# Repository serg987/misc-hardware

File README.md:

# misc-hardware

Collection of small hardware projects and KiCad designs developed as experimental ones

## Projects

- [mllse-m2-air-breakout-board](./mllse-m2-air-breakout-board/)
  - Breakout board and modification guide for the MLLSE M2 Air mini PC. Provides two full-size M.2 Key-B SATA slots and 
one M.2 Key-M PCIe x1 slot, includes KiCad project, BOM, gerbers, and step-by-step modification instructions.

- [radxa_a5e_m2_to_rasp_pcie](./radxa_a5e_m2_to_rasp_pcie/)
  - M.2 Key-M to Raspberry Pi PCIe adapter for the Radxa A5E SBC. Allows using Raspberry Pi PCIe HATs via a 
Raspberry Pi PCIe FPC cable.

## How to use

Each project contains its own `readme.md` with detailed information, KiCad project files, and media. 
Open the subproject folder and read its `readme.md` for design details, BOM, and assembly or modification instructions.

## License

This repository is covered by the project LICENSE. See `LICENSE` in the repository root for details.

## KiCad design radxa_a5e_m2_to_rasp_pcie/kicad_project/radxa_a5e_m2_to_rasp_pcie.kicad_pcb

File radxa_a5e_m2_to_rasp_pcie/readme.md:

# M.2 Key M to Raspberry Pi PCIe adapter

Allows use of Raspberry Pi HATs with the Radxa A5E SBC. Requires a Raspberry Pi PCIe FPC cable at least 40 mm long.

The board was manufactured and electrically tested — it is recognized by the Radxa A5E. Due to Radxa's limited 
third‑party support, development will not continue. The design can still serve as a baseline for other projects.

## BOM

- 16‑pin 0.5 mm 'bottom' FPC connector  
- Optional 5 V power-supply connector — any 2‑pin 1.0 mm pitch SMD connector

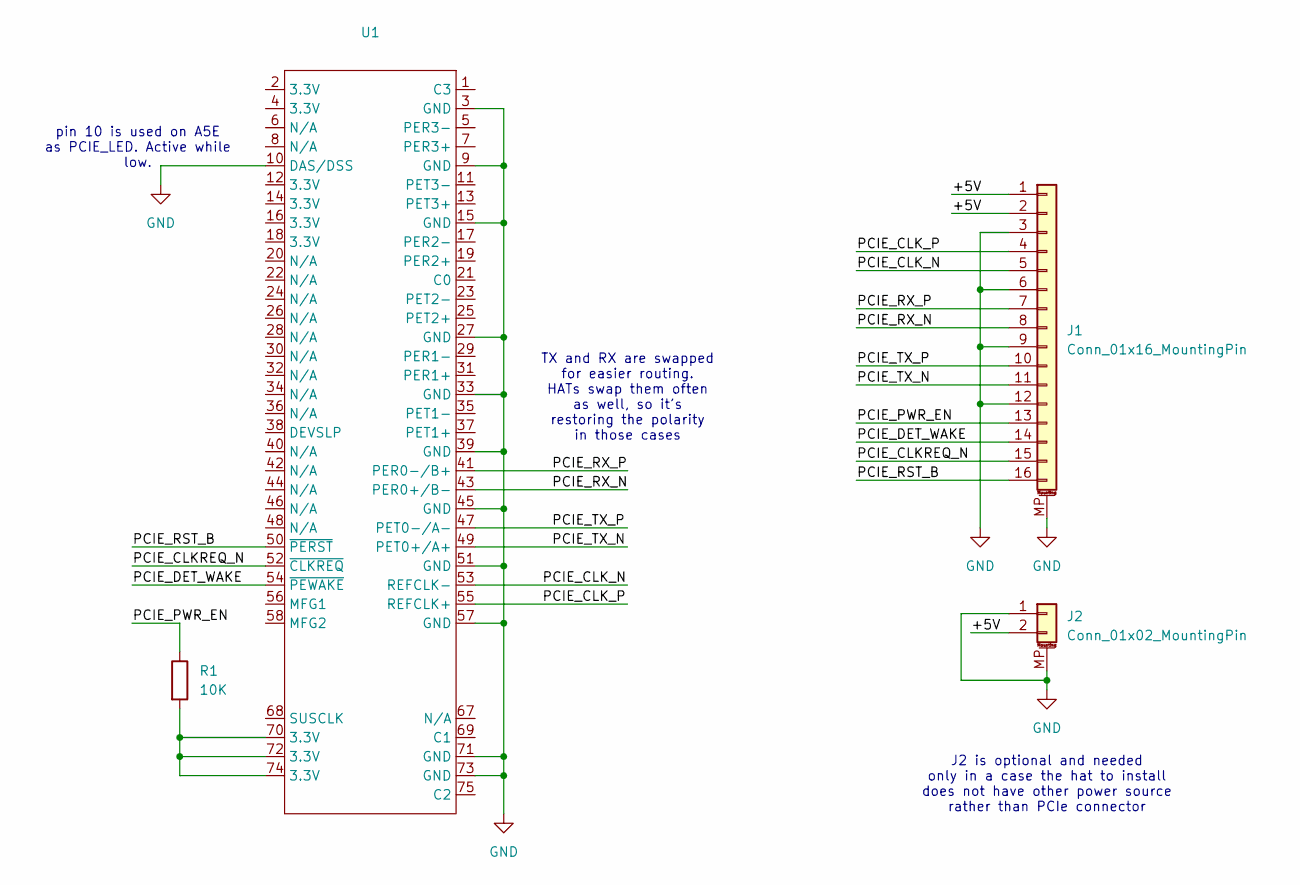
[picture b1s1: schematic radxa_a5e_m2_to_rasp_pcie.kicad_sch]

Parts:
J1: Conn_01x16_MountingPin; Amphenol_F32Q-1A7x1-11016_1x16-1MP_P0.5mm_Horizontal-revers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
J2: Conn_01x02_MountingPin; JST_SH_SM02B-SRSS-TB_1x02-1MP_P1.00mm_Horizontal
R1: 10K; R_1206_3216Metric_Pad1.30x1.75mm_HandSolder
U1: NGFF_M_LONG_NO_MASK

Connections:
/+5V: J1.1, J1.2, J2.2
/PCIE_CLKREQ_N: J1.15, U1.52 (~CLKREQ)
/PCIE_CLK_N: J1.5, U1.53 (REFCLK-)
/PCIE_CLK_P: J1.4, U1.55 (REFCLK+)
/PCIE_DET_WAKE: J1.14, U1.54 (~PEWAKE)
/PCIE_PWR_EN: J1.13, R1.1
/PCIE_RST_B: J1.16, U1.50 (~PERST)
/PCIE_RX_N: J1.8, U1.43 (PER0+/B-)
/PCIE_RX_P: J1.7, U1.41 (PER0-/B+)
/PCIE_TX_N: J1.11, U1.49 (PET0+/A+)
/PCIE_TX_P: J1.10, U1.47 (PET0-/A-)
GND: J1.3, J1.6, J1.9, J1.12, J1.MP (MountPin), J2.1, J2.MP (MountPin), U1.3 (GND), U1.9 (GND), U1.10 (DAS/DSS), U1.15 (GND), U1.27 (GND), U1.33 (GND), U1.39 (GND), U1.45 (GND), U1.51 (GND), U1.57 (GND), U1.71 (GND), U1.73 (GND)
unnamed: R1.2, U1.70 (3.3V), U1.72 (3.3V), U1.74 (3.3V)

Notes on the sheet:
TX and RX are swapped for easier routing. HATs swap them often as well, so it's restoring the polarity in those cases
pin 10 is used on A5E as PCIE_LED. Active while low.
J2 is optional and needed only in a case the hat to install does not have other power source rather than PCIe connector

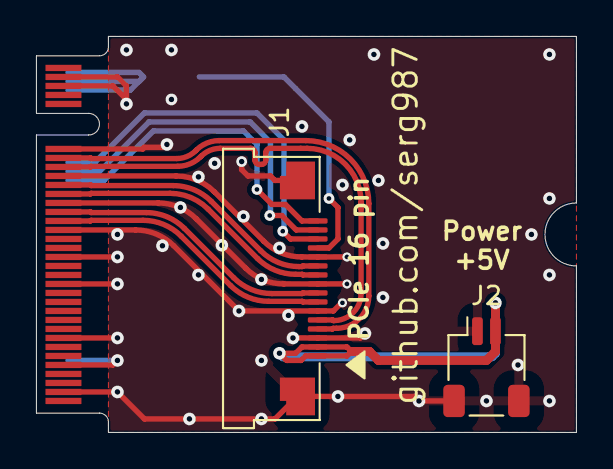
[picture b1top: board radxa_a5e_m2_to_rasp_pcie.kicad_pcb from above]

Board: 2 copper layers, 30.0 x 22.0 mm, 4 parts (1 on the bottom side), 13 nets.

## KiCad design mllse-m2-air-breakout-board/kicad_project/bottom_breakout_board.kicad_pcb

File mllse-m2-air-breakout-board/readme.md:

# M.2 Breakout Board for MLLSE M2 Air Mini PC

This project contains the design files and instructions for a breakout board that significantly expands the I/O 
capabilities of the MLLSE M2 Air Mini PC, a compact and affordable x86 machine ideal for homelab projects.

## Table of Contents

- [Motivation](#motivation)
- [Project Overview](#project-overview)
- [Disclaimer](#-disclaimer)
- [Compatibility](#compatibility)
- [The Breakout Board](#the-breakout-board)
  - [Features](#features)
  - [Onboard Power Supply](#onboard-power-supply)
  - [PCB Manufacturing](#pcb-manufacturing)
- [Mainboard Modification Guide](#mainboard-modification-guide)
  - [Step 1: Sourcing 12V Power](#step-1-sourcing-12v-power)
  - [Step 2: Preparing the PCIe Interface](#step-2-preparing-the-pcie-interface)
  - [Step 3: Preparing the Secondary SATA Interface](#step-3-preparing-the-secondary-sata-interface)
- [Bill of Materials (BOM)](#bill-of-materials-bom)
- [Known Issues](#known-issues)

## Motivation

Low-power, small-form-factor computers like mini PCs and Single-Board Computers (SBCs) are excellent choices for 
homelab setups. However, the market can be challenging to navigate. Powerful x86-based options with standard interfaces 
like PCIe and SATA are often expensive, while many non-x86 alternatives lack robust software support and documentation 
(with the notable exception of the Raspberry Pi).

A series of inexpensive Chinese mini PCs, such as the MLLSE M2 Air (based on Intel N4000/N3350 CPUs), offer a 
compelling alternative. They are passively cooled, affordable, and being native x86, they run most software without 
compatibility concerns. For a price comparable to a Raspberry Pi 5 kit, you get a complete system with an enclosure, 
heatsink, and power supply.

However, their primary limitation is a restrictive set of internal interfaces:
- A single M.2 Key-B slot (SATA only) that physically fits only small `<2242` modules.
- A proprietary, unpopulated SATA connector.
- No accessible PCIe lanes for expansion.

This project was born out of a desire to unlock the true potential of this hardware, transforming it from a limited 
device into a versatile server platform.

## Project Overview

This breakout board is designed to overcome the MLLSE M2 Air's I/O limitations. By interfacing with the existing M.2 
slot and repurposing connectors on the mainboard, it provides:

- **Two (2) full-size 2280 M.2 Key-B SATA slots.**
- **One (1) full-size 2280 M.2 Key-M PCIe x1 slot.**

With this board, the mini PC becomes a powerful and flexible platform. It can be used as a Network Video Recorder 
(NVR) with a Google Coral TPU in the PCIe slot and two SATA drives for storage, or as a mini NAS with up to three 
storage devices.

---

## ⚠️ Disclaimer

**This is an advanced hardware modification project that requires significant technical skill, including fine-pitch 
soldering with a hot air station. There is a high risk of permanently damaging your mini PC.**

**Proceed at your own risk. The author of this project assumes no liability for any damage to your equipment, lost time, 
or any other losses incurred while attempting this modification. Please evaluate your skills and equipment before 
starting.**

---

## Compatibility

This breakout board was designed specifically for the **MLLSE M2 Air, PCB version `MX-GB07 V100 20191009`**.

It is highly likely that other PCB versions or models based on different CPUs (e.g., N3350) have different layouts, 
and this board will **not** be compatible with them. While those boards may offer similar modification opportunities, 
they would require a new PCB to be designed from scratch.

## The Breakout Board

The breakout board neatly integrates into the system by plugging into the mainboard's original M.2 slot and is secured 
with M2 standoffs.

### Features

- **PCIe M.2 Key-M Slot:** Taps into the PCIe lanes originally used by the onboard Wi-Fi/Bluetooth module.
- **Two SATA M.2 Key-B Slots:** One slot uses the mainboard's original M.2 connection, and the second uses the 
unpopulated SATA header.
- **Onboard Power Supply:** A DC-DC buck converter provides the stable 3.3V power required for all three M.2 devices.

### Onboard Power Supply

The board includes a DC-DC buck converter based on the FR9889 IC to step down the mainboard's 12V input to the 3.3V 
needed by the M.2 devices. The converter's enable pin is connected to the 3.3V line of the mainboard's M.2 slot, 
ensuring the breakout board powers on and off with the host system.

**🚨 CRITICAL PRECAUTION: After assembling the breakout board, always test the output voltage of the DC-DC converter 
*before* installing any M.2 devices. Ensure it provides a stable 3.3V.**

### PCB Manufacturing

The PCB is designed to be 100x100mm to take advantage of promotional pricing from many manufacturers. It is essential 
that the board is manufactured with a **thickness of 0.8mm**.

The Gerbers can be found in the `/gerbers` directory. You can order the board from PCBWAY with this 
[link](https://www.pcbway.com/project/shareproject/MLLSE_M2_Air_Triple_M_2_Expansion_Breakout_Board_1323e575.html).

## Mainboard Modification Guide

### Step 1: Sourcing 12V Power

The easiest place to get a 12V supply for the breakout board is directly from the main DC input jack.

### Step 2: Preparing the PCIe Interface

This is the most challenging part of the modification. It requires desoldering the onboard Wi-Fi/Bluetooth module to 
access the PCIe lanes.

1.  **Remove the Wi-Fi Module:** Use a hot air station to carefully desolder the Wi-Fi module. Be aware of the multiple 
ground pads underneath the module and the many small passive components surrounding it. Avoid damaging the 
signal pads.
2.  **Solder the FPC Connector:** Once the module is removed, you need to solder a **16-pin, 0.5mm pitch, 
'bottom' FPC connector**. This connector type and its precise placement are crucial for compatibility with standard 
Raspberry Pi PCIe FPC cables.
    - **Critical Placement:** The connector must be soldered with a **1-pin offset**. Pin 2 of the FPC connector 
should align with pad 29 of the Wi-Fi module footprint.
    - **Insulation:** The underside of the FPC connector may have exposed metal. You must insulate the mainboard pads 
underneath it to prevent short circuits. This means the connector's mounting pads will not be soldered, so handle the 
final connection with care.

A **3cm Raspberry Pi PCIe FPC cable** is sufficient for connecting the mainboard to the breakout board. The breakout 
board requires a **16-pin, 0.5mm pitch, 'top' FPC connector**.

### Step 3: Preparing the Secondary SATA Interface

The unpopulated SATA connector on the mainboard has a rare 0.8mm pitch, making it difficult to find a matching 
connector.

1.  **Use a Solderable FPC:** The most practical solution is to use a 7-pin, 0.8mm pitch solderable FPC cable. 
This creates a permanent, non-flexible connection but is reliable.
2.  **Short Empty Pads:** The SATA signal lanes on the mainboard have empty `0201` component footprints. These must 
be shorted for the signal to pass through. It is best to use `0-ohm 0201` resistors, but a small jumper wire can 
also work.

## Bill of Materials (BOM)

The following components are required to fully assemble the breakout board. The links provided are for illustrative purposes only and are not an endorsement.

| Quantity | Component                                     | Notes                                           | Example Link                                             |
| -------- |-----------------------------------------------| ----------------------------------------------- | -------------------------------------------------------- |
| 6+       | M2 Standoffs, H=2.5mm                         | For mounting the board.                         | [AliExpress](https://www.aliexpress.us/item/3256807359356659.html) |
| 1        | 7-pin Solderable FPC Cable, 0.8mm pitch, 40mm | For the secondary SATA connection.              | [AliExpress](https://www.aliexpress.us/item/3256805836297968.html) |
| 1        | Raspberry Pi PCIe FPC Cable, 30mm             | For the PCIe connection.                        | [AliExpress](https://www.aliexpress.us/item/3256808358195550.html) |
| 1        | FR9889 IC                                     | DC-DC Buck Converter.                           | [AliExpress](https://www.aliexpress.us/item/3256806733161105.html) |
| 1        | 16-Pin FPC Connector, 0.5mm, Top              | For the breakout board's PCIe input.            | [AliExpress](https://www.aliexpress.us/item/3256803795508780.html) |
| 1        | 16-Pin FPC Connector, 0.5mm, Bottom           | For the mainboard's PCIe output.                | [AliExpress](https://www.aliexpress.us/item/3256803795508780.html) |
| 2        | M.2 Key-B Slot, H=4.2mm                       | Height may vary based on standoffs used.        | [AliExpress](https://www.aliexpress.us/item/3256808634409928.html) |
| 1        | M.2 Key-M Slot, H=4.2mm                       | Height may vary based on standoffs used.        | [AliExpress](https://www.aliexpress.us/item/3256808634409928.html) |
| 1        | JST PH Connector, 2-pin, 2.0mm                | For 12V power input.                            | [AliExpress](https://www.aliexpress.us/item/3256808498055527.html) |
| 1        | Inductor, 10uH                                | Wuerth_HCI-1040 or equivalent.                  | -                                                        |
| 2        | Capacitor, 10uF 35V                           | Size B / 1411                                   | -                                                        |
| 7        | Capacitor, 33uF 16V                           | Size A / 1206                                   | -                                                        |
| 11       | Capacitor, 100nF                              | 1206                                            | -                                                        |
| 1        | Resistor, 8.2kΩ                               | 1206                                            | -                                                        |
| 2        | Resistor, 10kΩ                                | 1206                                            | -                                                        |
| 1        | Resistor, 18kΩ                                | 1206                                            | -                                                        |
| 1        | Resistor, 33kΩ                                | 1206                                            | -                                                        |
| 1        | Resistor, 100kΩ                               | 1206                                            | -                                                        |
| 1        | Diode, 1N4148                                 | Optional, for 5V power supply protection.       | -                                                        |

## Known Issues

- **Mounting Hole Alignment:** The mounting holes on the initial PCB version may not be perfectly aligned with those on 
the mainboard. The KiCad project has been updated with corrected positions, but this revision has not yet been 
manufactured and tested.
- **Battery Clearance:** The mainboard's coin cell battery may be glued in a position that interferes with the breakout 
board. Although a tolerance gap has been designed into the board, you may need to carefully reposition the battery.

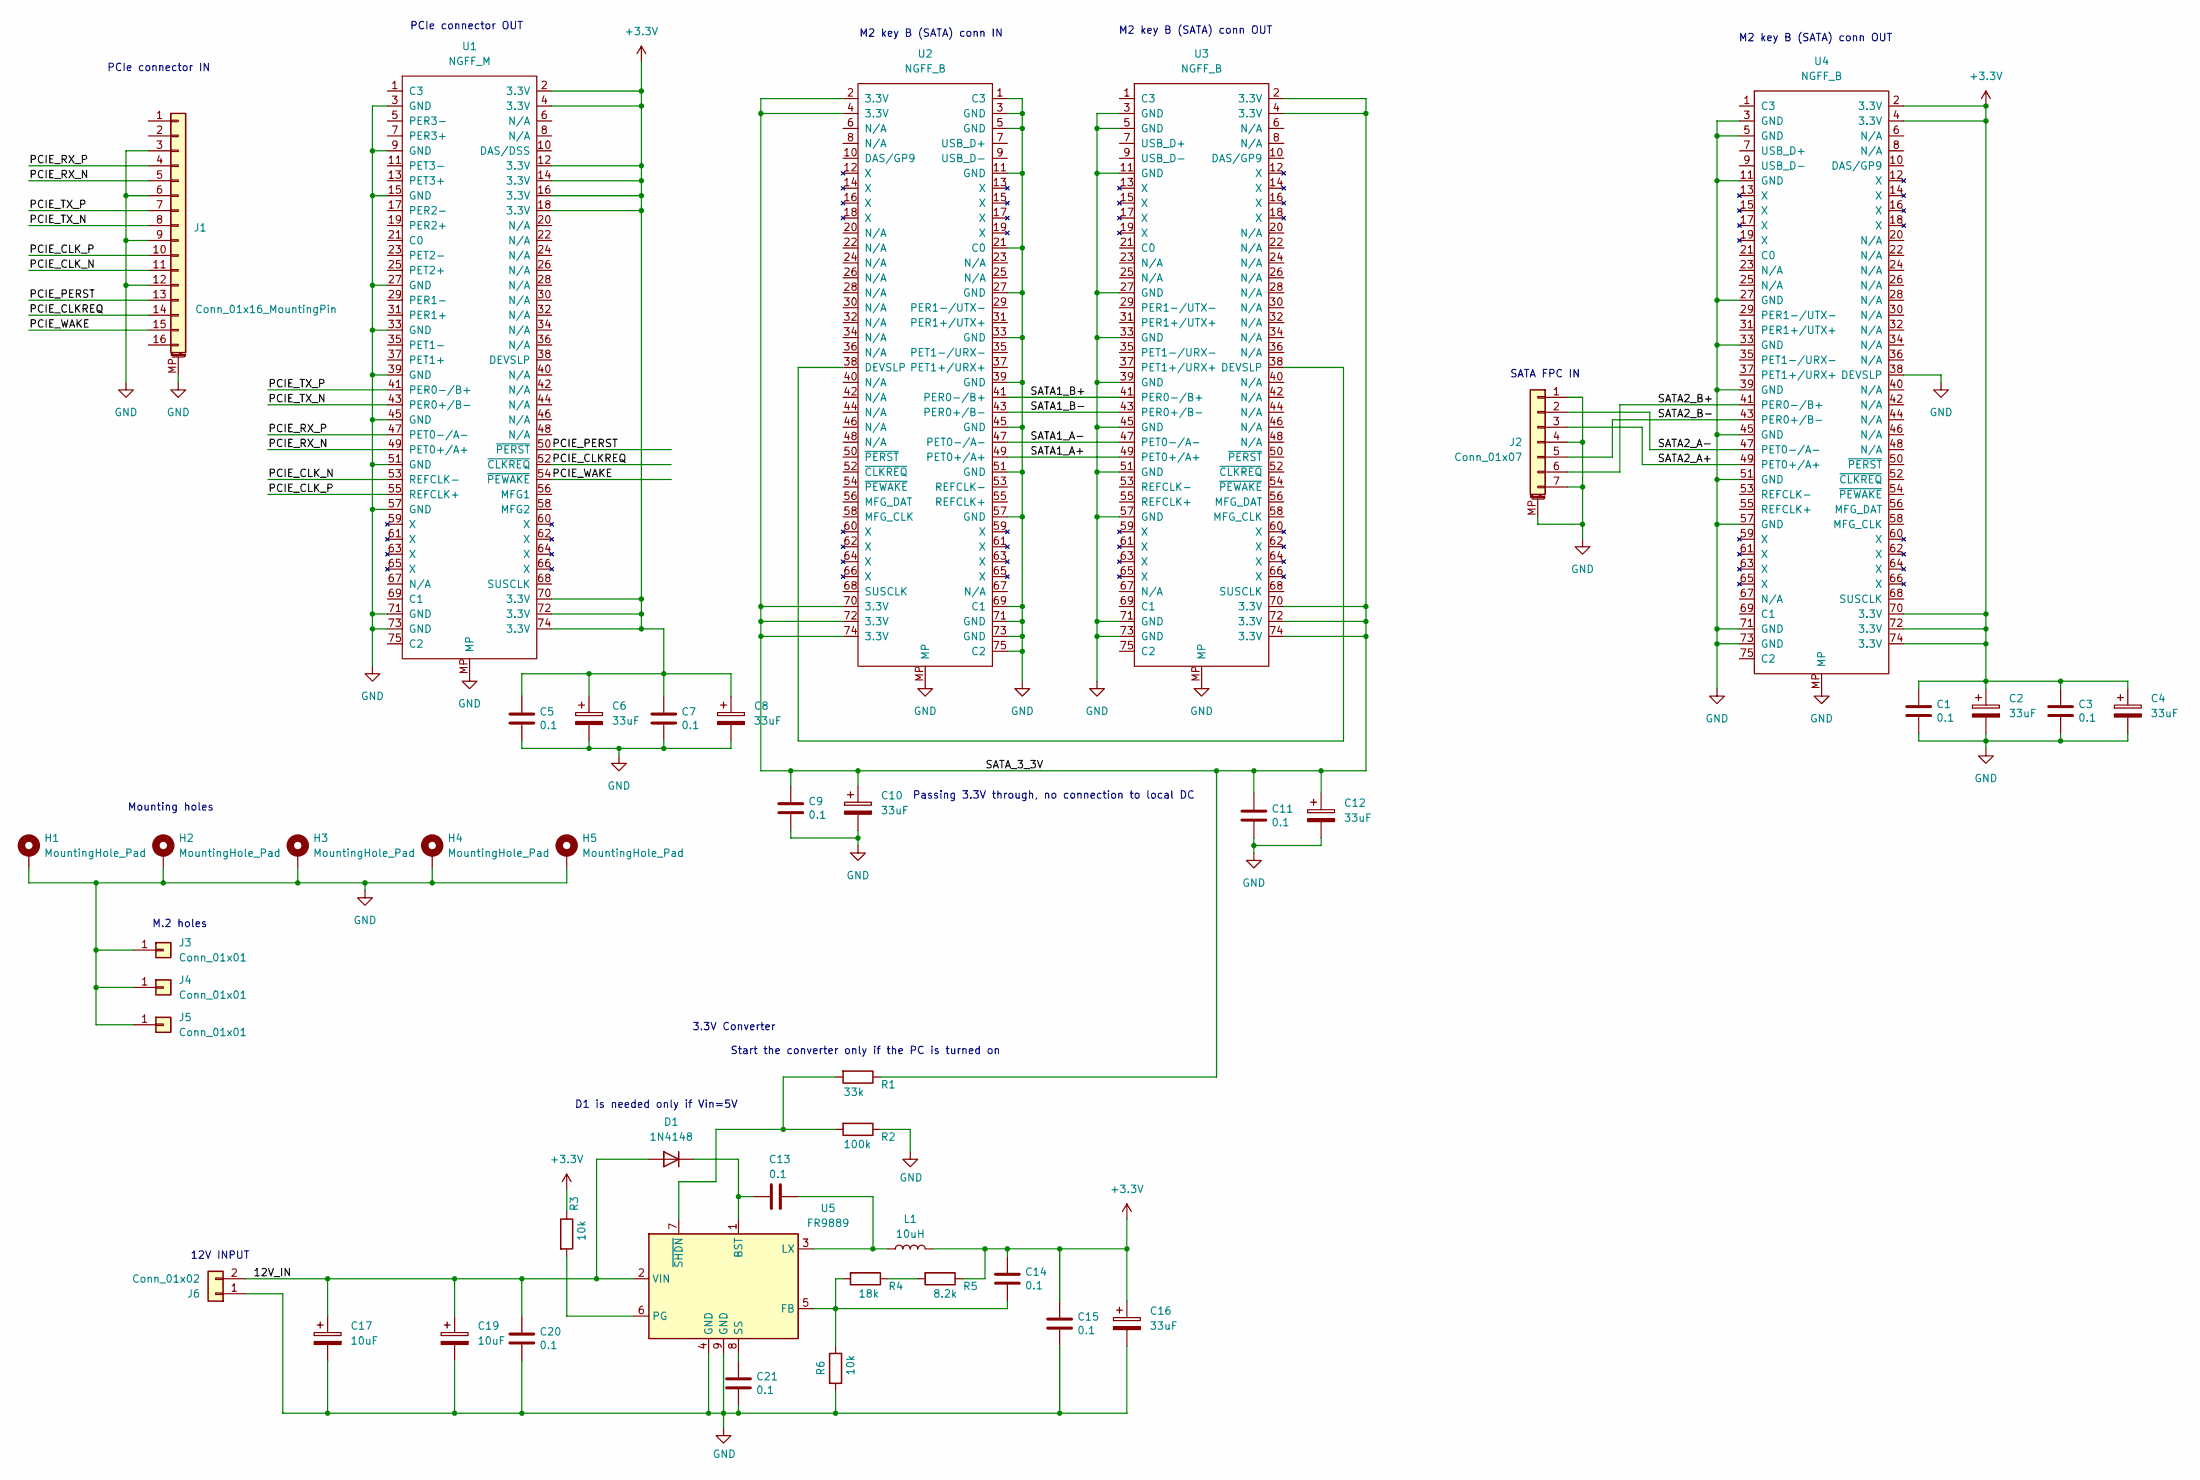
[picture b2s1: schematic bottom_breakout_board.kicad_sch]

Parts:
C1, C3, C5, C7, C9, C11, C13, C14, C15, C20, C21: 0.1; C_1206_3216Metric_Pad1.33x1.80mm_HandSolder
C2, C4, C6, C8, C10, C12, C16: 33uF; C_1206_3216Metric_Pad1.33x1.80mm_HandSolder
C17, C19: 10uF; CP_EIA-6032-28_Kemet-C_HandSolder
D1: 1N4148; D_1206_3216Metric_Pad1.42x1.75mm_HandSolder
H1, H2, H3, H4, H5: MountingHole_Pad; MountingHole_3.2mm_M3_ISO7380_Pad
J1: Conn_01x16_MountingPin; Amphenol_F32Q-1A7x1-11016_1x16-1MP_P0.5mm_Horizontal
J2: Conn_01x07; FPC_P0.80mm_Horizontal
J3, J4, J5: Conn_01x01; M.2-Card_boundaries
J6: Conn_01x02; JST_PH_S2B-PH-K_1x02_P2.00mm_Horizontal
L1: 10uH; L_Wuerth_HCI-1040
R1: 33k; R_1206_3216Metric_Pad1.30x1.75mm_HandSolder
R2: 100k; R_1206_3216Metric_Pad1.30x1.75mm_HandSolder
R3, R6: 10k; R_1206_3216Metric_Pad1.30x1.75mm_HandSolder
R4: 18k; R_1206_3216Metric_Pad1.30x1.75mm_HandSolder
R5: 8.2k; R_1206_3216Metric_Pad1.30x1.75mm_HandSolder
U1: NGFF_M; Conn_TE-M.2-0.5-67P-doublesided_TypeM
U2: NGFF_B
U3, U4: NGFF_B; Conn_TE-M.2-0.5-67P-doublesided_TypeB
U5: FR9889; HSOP-8-1EP_3.9x4.9mm_P1.27mm_EP2.41x3.1mm_ThermalVias

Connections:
+3.3V: C1.1, C2.1, C3.1, C4.1, C5.1, C6.1, C7.1, C8.1, C14.1, C15.1, C16.1, L1.2, R3.1, R5.1, U1.2 (3.3V), U1.4 (3.3V), U1.12 (3.3V), U1.14 (3.3V), U1.16 (3.3V), U1.18 (3.3V), U1.70 (3.3V), U1.72 (3.3V), U1.74 (3.3V), U4.2 (3.3V), U4.4 (3.3V), U4.70 (3.3V), U4.72 (3.3V), U4.74 (3.3V)
/12V_IN: C17.1, C19.1, C20.1, D1.2 (A), J6.2, U5.2 (VIN)
/PCIE_CLKREQ: J1.14, U1.52 (~CLKREQ)
/PCIE_CLK_N: J1.11, U1.53 (REFCLK-)
/PCIE_CLK_P: J1.10, U1.55 (REFCLK+)
/PCIE_PERST: J1.13, U1.50 (~PERST)
/PCIE_RX_N: J1.5, U1.49 (PET0+/A+)
/PCIE_RX_P: J1.4, U1.47 (PET0-/A-)
/PCIE_TX_N: J1.8, U1.43 (PER0+/B-)
/PCIE_TX_P: J1.7, U1.41 (PER0-/B+)
/PCIE_WAKE: J1.15, U1.54 (~PEWAKE)
/SATA1_A+: U2.49 (PET0+/A+), U3.49 (PET0+/A+)
/SATA1_A-: U2.47 (PET0-/A-), U3.47 (PET0-/A-)
/SATA1_B+: U2.41 (PER0-/B+), U3.41 (PER0-/B+)
/SATA1_B-: U2.43 (PER0+/B-), U3.43 (PER0+/B-)
/SATA2_A+: J2.3, U4.49 (PET0+/A+)
/SATA2_A-: J2.2, U4.47 (PET0-/A-)
/SATA2_B+: J2.6, U4.41 (PER0-/B+)
/SATA2_B-: J2.5, U4.43 (PER0+/B-)
/SATA_3_3V: C9.1, C10.1, C11.1, C12.1, R1.1, U2.2 (3.3V), U2.4 (3.3V), U2.70 (3.3V), U2.72 (3.3V), U2.74 (3.3V), U3.2 (3.3V), U3.4 (3.3V), U3.70 (3.3V), U3.72 (3.3V), U3.74 (3.3V)
GND: C1.2, C2.2, C3.2, C4.2, C5.2, C6.2, C7.2, C8.2, C9.2, C10.2, C11.2, C12.2, C15.2, C16.2, C17.2, C19.2, C20.2, C21.2, H1.1, H2.1, H3.1, H4.1, H5.1, J1.3, J1.6, J1.9, J1.12, J1.MP (MountPin), J2.1, J2.4, J2.7, J2.MP (MountPin), J3.1, J4.1, J5.1, J6.1, R2.1, R6.2, U1.3 (GND), U1.9 (GND), U1.15 (GND), U1.27 (GND), U1.33 (GND), U1.39 (GND), U1.45 (GND), U1.51 (GND), U1.57 (GND), U1.71 (GND), U1.73 (GND), U1.MP, U2.1 (C3), U2.3 (GND), U2.5 (GND), U2.11 (GND), U2.21 (C0), U2.27 (GND), U2.33 (GND), U2.39 (GND), U2.45 (GND), U2.51 (GND), U2.57 (GND), U2.69 (C1), U2.71 (GND), U2.73 (GND), U2.75 (C2), U2.MP, U3.3 (GND), U3.5 (GND), U3.11 (GND), U3.27 (GND), U3.33 (GND), U3.39 (GND), U3.45 (GND), U3.51 (GND), U3.57 (GND), U3.71 (GND), U3.73 (GND), U3.MP, U4.3 (GND), U4.5 (GND), U4.11 (GND), U4.27 (GND), U4.33 (GND), U4.38 (DEVSLP), U4.39 (GND), U4.45 (GND), U4.51 (GND), U4.57 (GND), U4.71 (GND), U4.73 (GND), U4.MP, U5.4 (GND), U5.9 (GND)
unnamed: C13.1, D1.1 (K), U5.1 (BST)
unnamed: R4.1, R5.2
unnamed: U2.38 (DEVSLP), U3.38 (DEVSLP)
unnamed: C14.2, R4.2, R6.1, U5.5 (FB)
unnamed: C13.2, L1.1, U5.3 (LX)
unnamed: R3.2, U5.6 (PG)
unnamed: C21.1, U5.8 (SS)
unnamed: R1.2, R2.2, U5.7 (~SHDN)

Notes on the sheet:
PCIe connector OUT
M2 key B (SATA) conn OUT
Start the converter only if the PC is turned on
3.3V Converter
Passing 3.3V through, no connection to local DC
12V INPUT
PCIe connector IN
M.2 holes
D1 is needed only if Vin=5V
M2 key B (SATA) conn IN
Mounting holes
SATA FPC IN

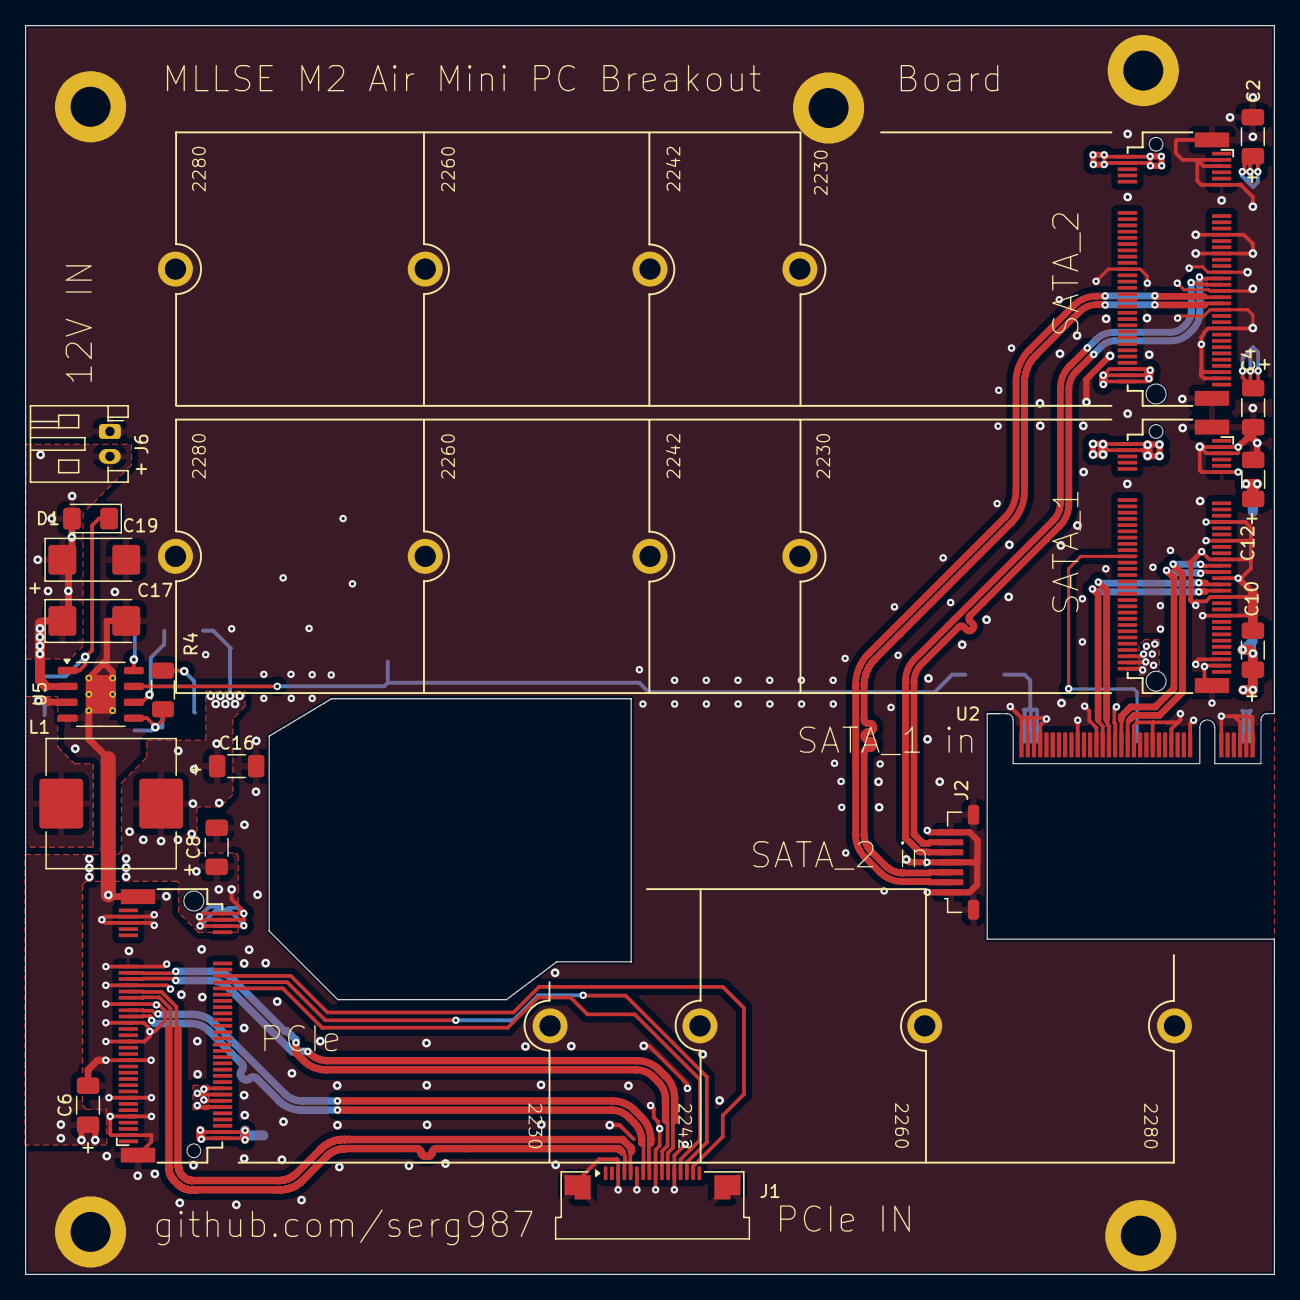
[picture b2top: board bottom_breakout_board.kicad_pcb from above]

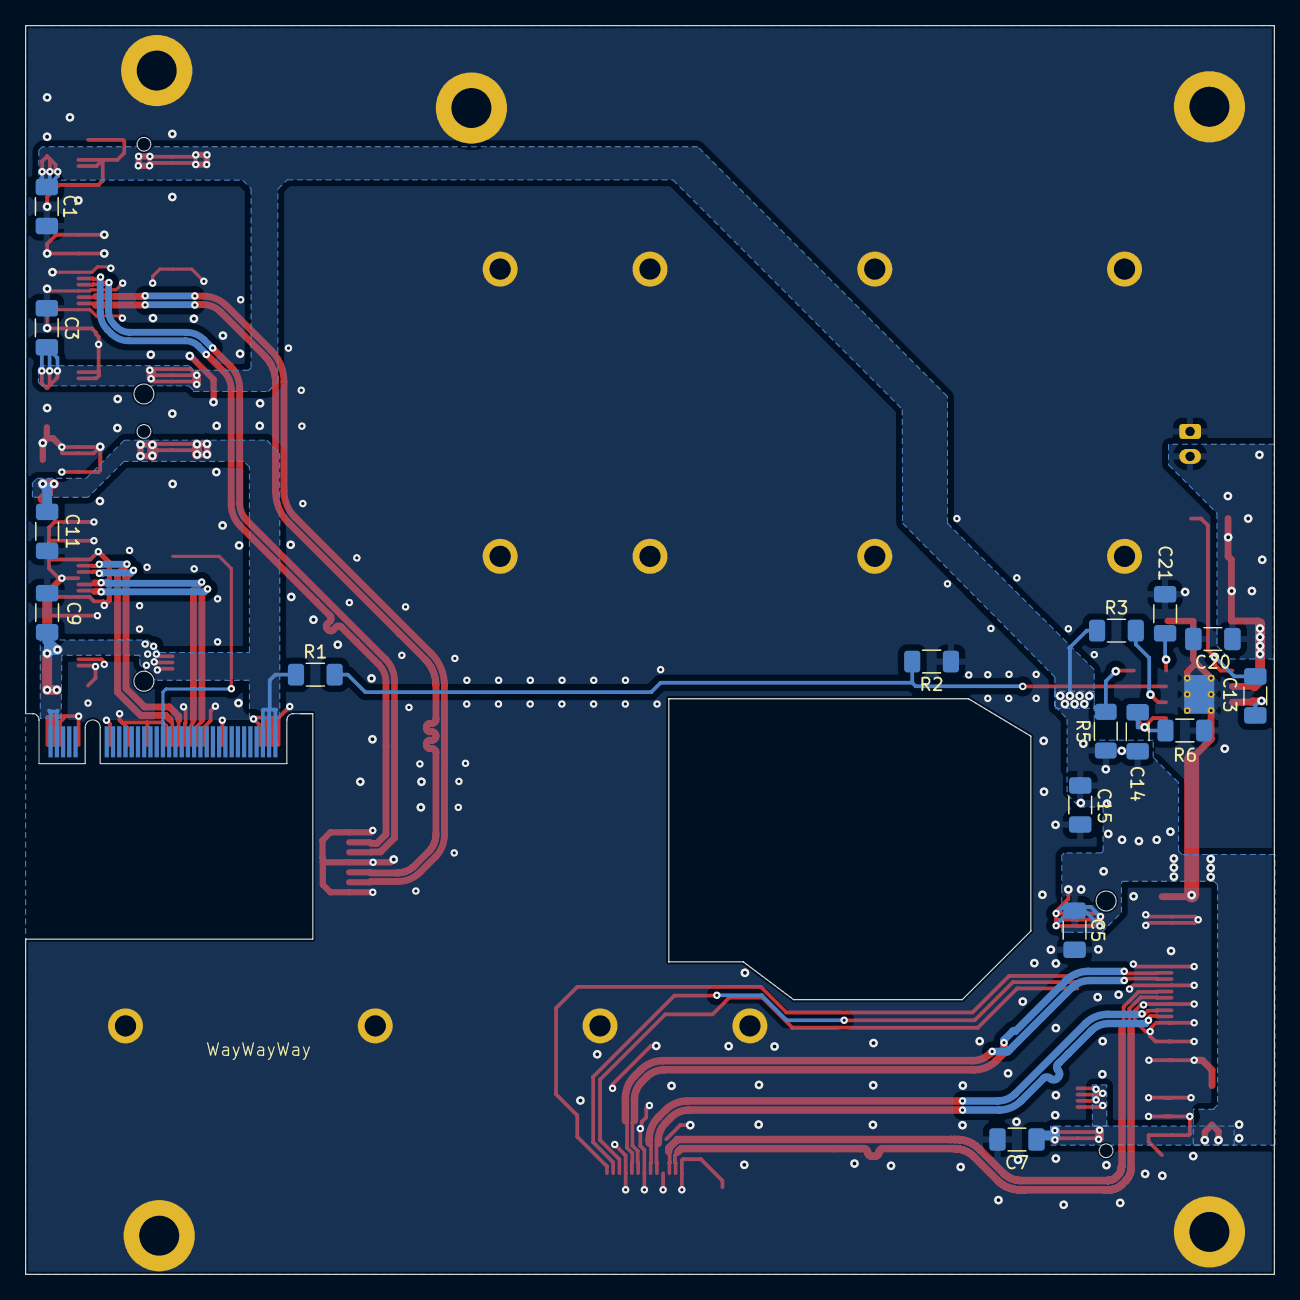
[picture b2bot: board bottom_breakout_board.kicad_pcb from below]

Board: 2 copper layers, 100.0 x 100.0 mm, 44 parts (16 on the bottom side), 29 nets.

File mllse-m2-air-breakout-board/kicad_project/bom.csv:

"Reference","Qty","Value","DNP","Exclude from BOM","Exclude from Board","Footprint","Datasheet"
"C1,C3,C5,C7,C9,C11,C13,C14,C15,C20,C21","11","0.1","","","","Capacitor_SMD:C_1206_3216Metric_Pad1.33x1.80mm_HandSolder","~"
"C2,C4,C6,C8,C10,C12,C16","7","33uF","","","","Capacitor_SMD:C_1206_3216Metric_Pad1.33x1.80mm_HandSolder","~"
"C17,C19","2","10uF","","","","Capacitor_Tantalum_SMD:CP_EIA-6032-28_Kemet-C_HandSolder","~"
"D1","1","1N4148","","","","Diode_SMD:D_1206_3216Metric_Pad1.42x1.75mm_HandSolder","https://assets.nexperia.com/documents/data-sheet/1N4148_1N4448.pdf"
"H1,H2,H3,H4,H5","5","MountingHole_Pad","","Excluded from BOM","","MountingHole:MountingHole_3.2mm_M3_ISO7380_Pad","~"
"J1","1","Conn_01x16_MountingPin","","","","Connector_FFC-FPC:Amphenol_F32Q-1A7x1-11016_1x16-1MP_P0.5mm_Horizontal","~"
"J2","1","Conn_01x07","","Excluded from BOM","","user_lib:FPC_P0.80mm_Horizontal","~"
"J3,J4,J5","3","Conn_01x01","","","","user_lib:M.2-Card_boundaries","~"
"J6","1","Conn_01x02","","","","Connector_JST:JST_PH_S2B-PH-K_1x02_P2.00mm_Horizontal","~"
"L1","1","10uH","","","","Inductor_SMD:L_Wuerth_HCI-1040","~"
"R1","1","33k","","","","Resistor_SMD:R_1206_3216Metric_Pad1.30x1.75mm_HandSolder","~"
"R2","1","100k","","","","Resistor_SMD:R_1206_3216Metric_Pad1.30x1.75mm_HandSolder","~"
"R3,R6","2","10k","","","","Resistor_SMD:R_1206_3216Metric_Pad1.30x1.75mm_HandSolder","~"
"R4","1","18k","","","","Resistor_SMD:R_1206_3216Metric_Pad1.30x1.75mm_HandSolder","~"
"R5","1","8.2k","","","","Resistor_SMD:R_1206_3216Metric_Pad1.30x1.75mm_HandSolder","~"
"U1","1","NGFF_M","","","","user_lib:Conn_TE-M.2-0.5-67P-doublesided_TypeM",""
"U2","1","NGFF_B","","","","user_lib:NGFF_B",""
"U3,U4","2","NGFF_B","","","","user_lib:Conn_TE-M.2-0.5-67P-doublesided_TypeB",""
"U5","1","FR9889","","","","Package_SO:HSOP-8-1EP_3.9x4.9mm_P1.27mm_EP2.41x3.1mm_ThermalVias","https://datasheet.lcsc.com/lcsc/2004210832_Fitipower-Integra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"

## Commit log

2025-12-26 Add pcbway link
